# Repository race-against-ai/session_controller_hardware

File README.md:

# raai_session_controller_hardware

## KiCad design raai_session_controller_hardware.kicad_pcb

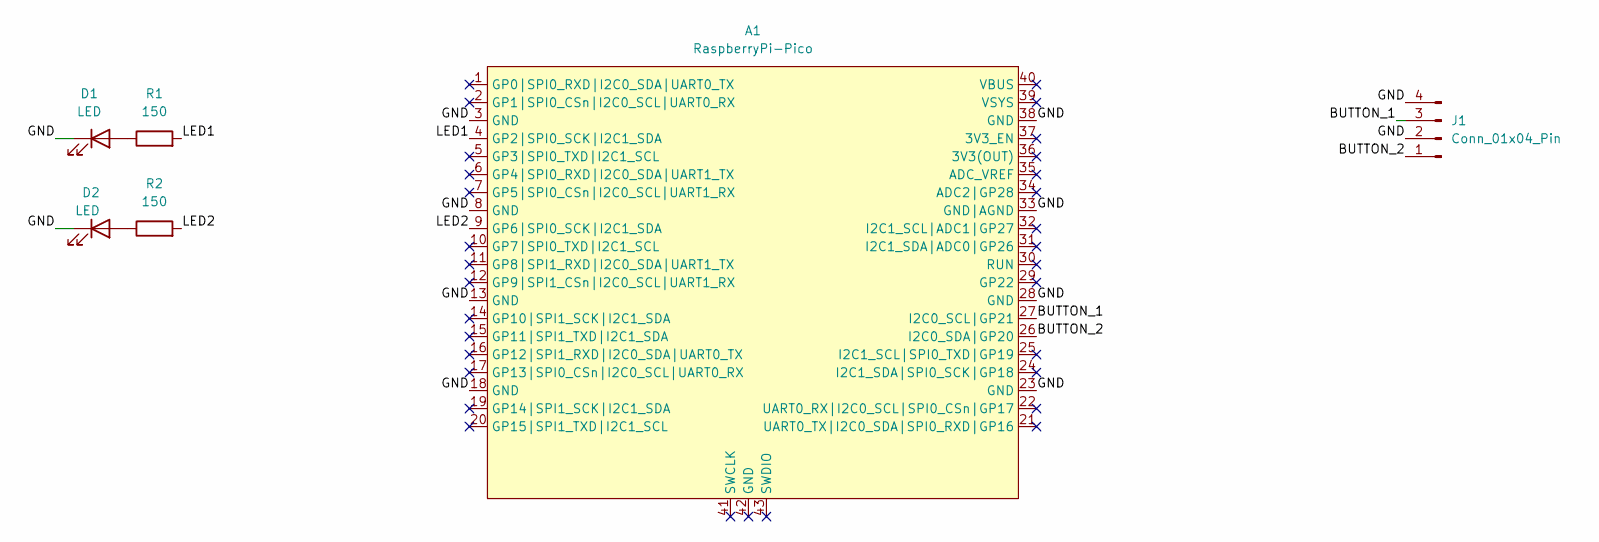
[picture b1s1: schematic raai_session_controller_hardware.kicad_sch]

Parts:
A1: RaspberryPi-Pico; RaspberryPiPico-THT-Dev
D1, D2: LED; LED_D3.0mm
J1: Conn_01x04_Pin; PinSocket_1x04_P2.54mm_Vertical
R1, R2: 150; R_Axial_DIN0204_L3.6mm_D1.6mm_P5.08mm_Horizontal

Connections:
/BUTTON_1: A1.27 (I2C0_SCL|GP21), J1.3
/BUTTON_2: A1.26 (I2C0_SDA|GP20), J1.1
/GND: A1.3 (GND), A1.8 (GND), A1.13 (GND), A1.18 (GND), A1.23 (GND), A1.28 (GND), A1.33 (GND|AGND), A1.38 (GND), D1.1 (K), D2.1 (K), J1.2, J1.4
/LED1: A1.4 (GP2|SPI0_SCK|I2C1_SDA), R1.2
/LED2: A1.9 (GP6|SPI0_SCK|I2C1_SDA), R2.2
unnamed: D1.2 (A), R1.1
unnamed: D2.2 (A), R2.1

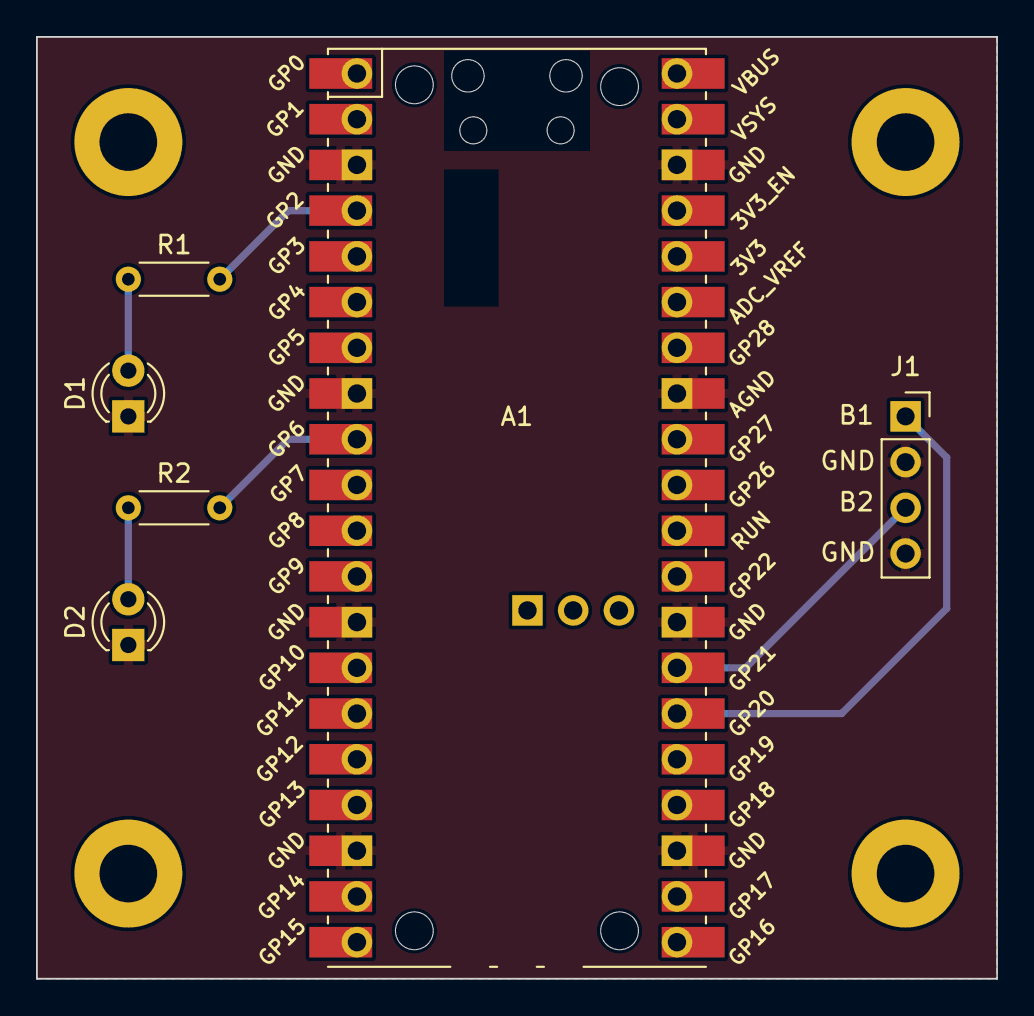
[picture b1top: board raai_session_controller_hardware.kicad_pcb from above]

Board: 2 copper layers, 53.3 x 52.3 mm, 6 parts (0 on the bottom side), 7 nets.

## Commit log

2023-12-14 First draft of pcb
2023-12-20 Final pcb design
2024-01-07 Updated RPI PicoW footprint and minor improvements
2024-01-07 Removed venv
2024-01-07 Adjusted project name
2025-01-06 Create LICENSE
